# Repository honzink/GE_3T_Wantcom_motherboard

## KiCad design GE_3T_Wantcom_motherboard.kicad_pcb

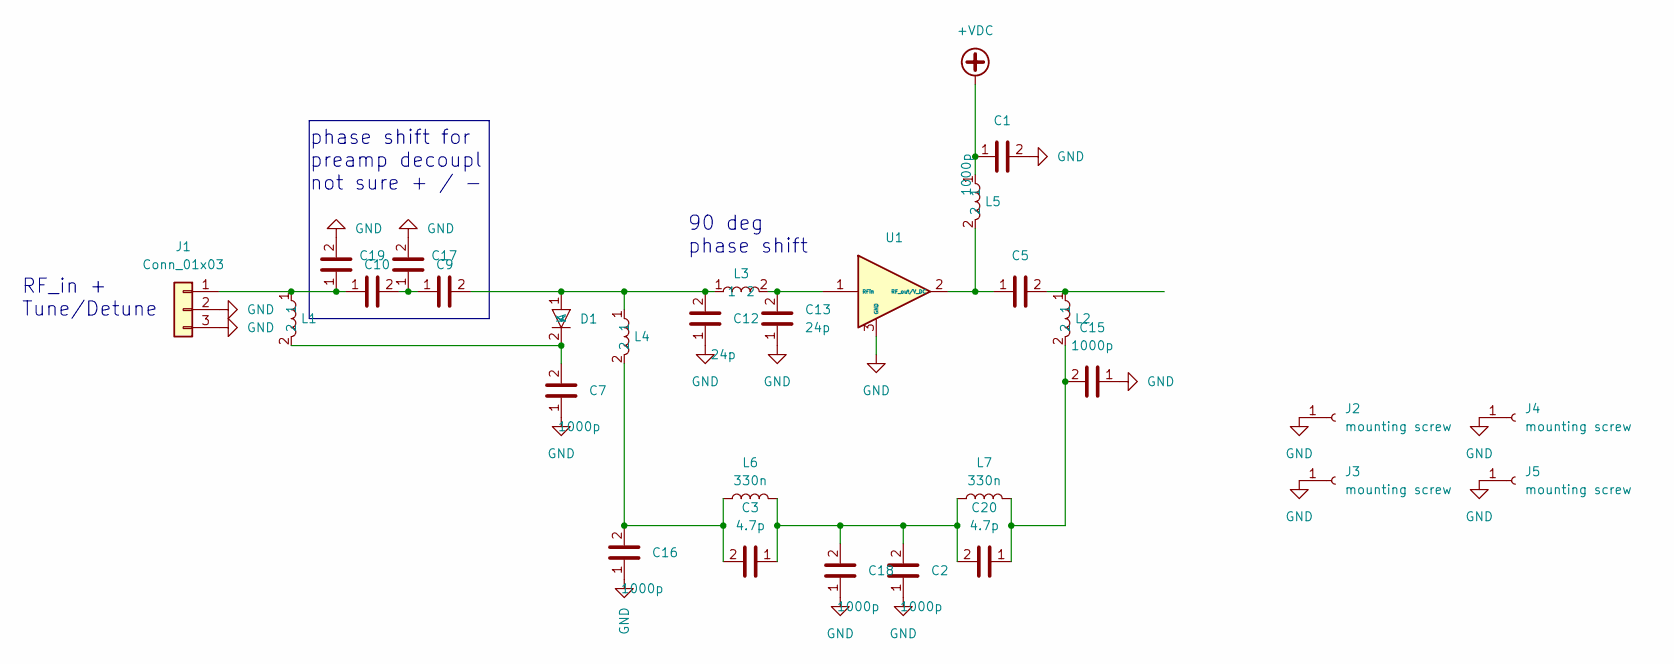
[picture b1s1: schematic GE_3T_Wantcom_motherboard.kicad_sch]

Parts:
C1, C2, C15, C16, C18: 1000p; C_0603_1608Metric
C3, C20: 4.7p; C_0603_1608Metric
C5, C9, C10, C17, C19: CAP_1111_HIQ_KNO
C7: 1000p; CAP_1111_HIQ_KNO
C12, C13: 24p; CAP_1111_HIQ_KNO
D1: PIN_diode_NonMagnetic_HighPower
J1: Conn_01x03; CONN1_UFL-R_HIR
J2, J3, J4, J5: mounting screw; screw head 440
L1, L2, L4, L5: L_1812_4532Metric
L3: L_0805_2012Metric
L6, L7: 330n; L_0603_1608Metric
U1: WANTCOM_WMM3RP

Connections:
+VDC: C1.1, L5.1
GND: C1.2, C2.1, C7.1, C9.2, C10.2, C12.1, C13.1, C15.1, C16.1, C18.1, J1.2, J1.3, J2.1, J3.1, J4.1, J5.1, U1.3 (GND)
unnamed: C5.2, L2.1
unnamed: C15.2, C20.1, L2.2, L7.2
unnamed: C3.2, C16.2, L4.2, L6.1
unnamed: C9.1, C17.1, C19.2
unnamed: C2.2, C3.1, C18.2, C20.2, L6.2, L7.1
unnamed: C12.2, C17.2, D1.1 (A), L3.1, L4.1
unnamed: C7.2, D1.2 (K), L1.2
unnamed: C10.1, C19.1, J1.1, L1.1
unnamed: C5.1, L5.2, U1.2 (RF_out/V_DC)
unnamed: C13.2, L3.2, U1.1 (RFin)

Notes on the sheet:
phase shift for preamp decoupl not sure + / -
RF_in + Tune/Detune
90 deg phase shift

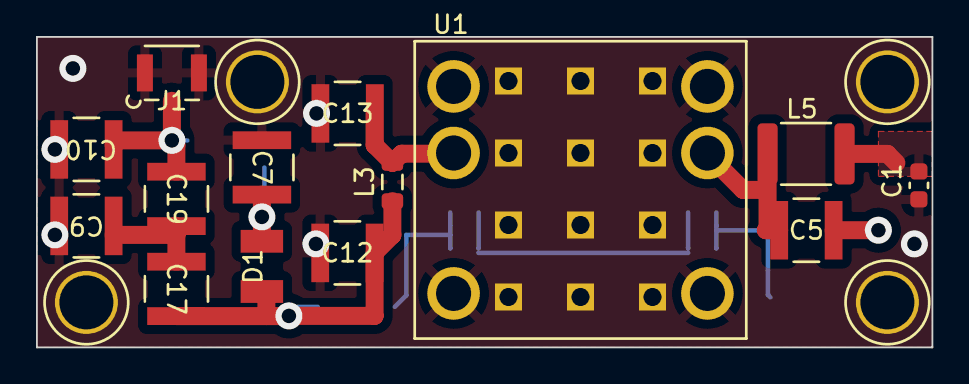
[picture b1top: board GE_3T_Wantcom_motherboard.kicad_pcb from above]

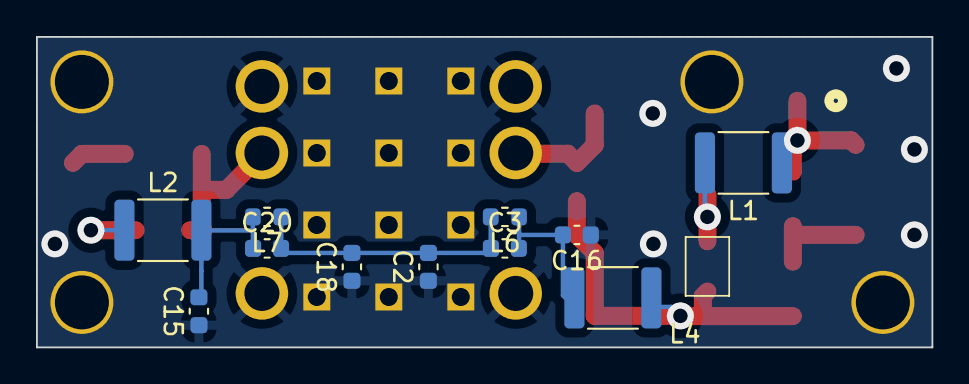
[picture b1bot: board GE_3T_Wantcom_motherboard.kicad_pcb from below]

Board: 2 copper layers, 49.8 x 17.2 mm, 29 parts (11 on the bottom side), 12 nets.

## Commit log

2023-11-24 Hello World
2023-11-25 board with screws, silkscreen issues
2023-11-27 board with screws better placement, silkscreen issues
2023-11-27 board before fabrication
